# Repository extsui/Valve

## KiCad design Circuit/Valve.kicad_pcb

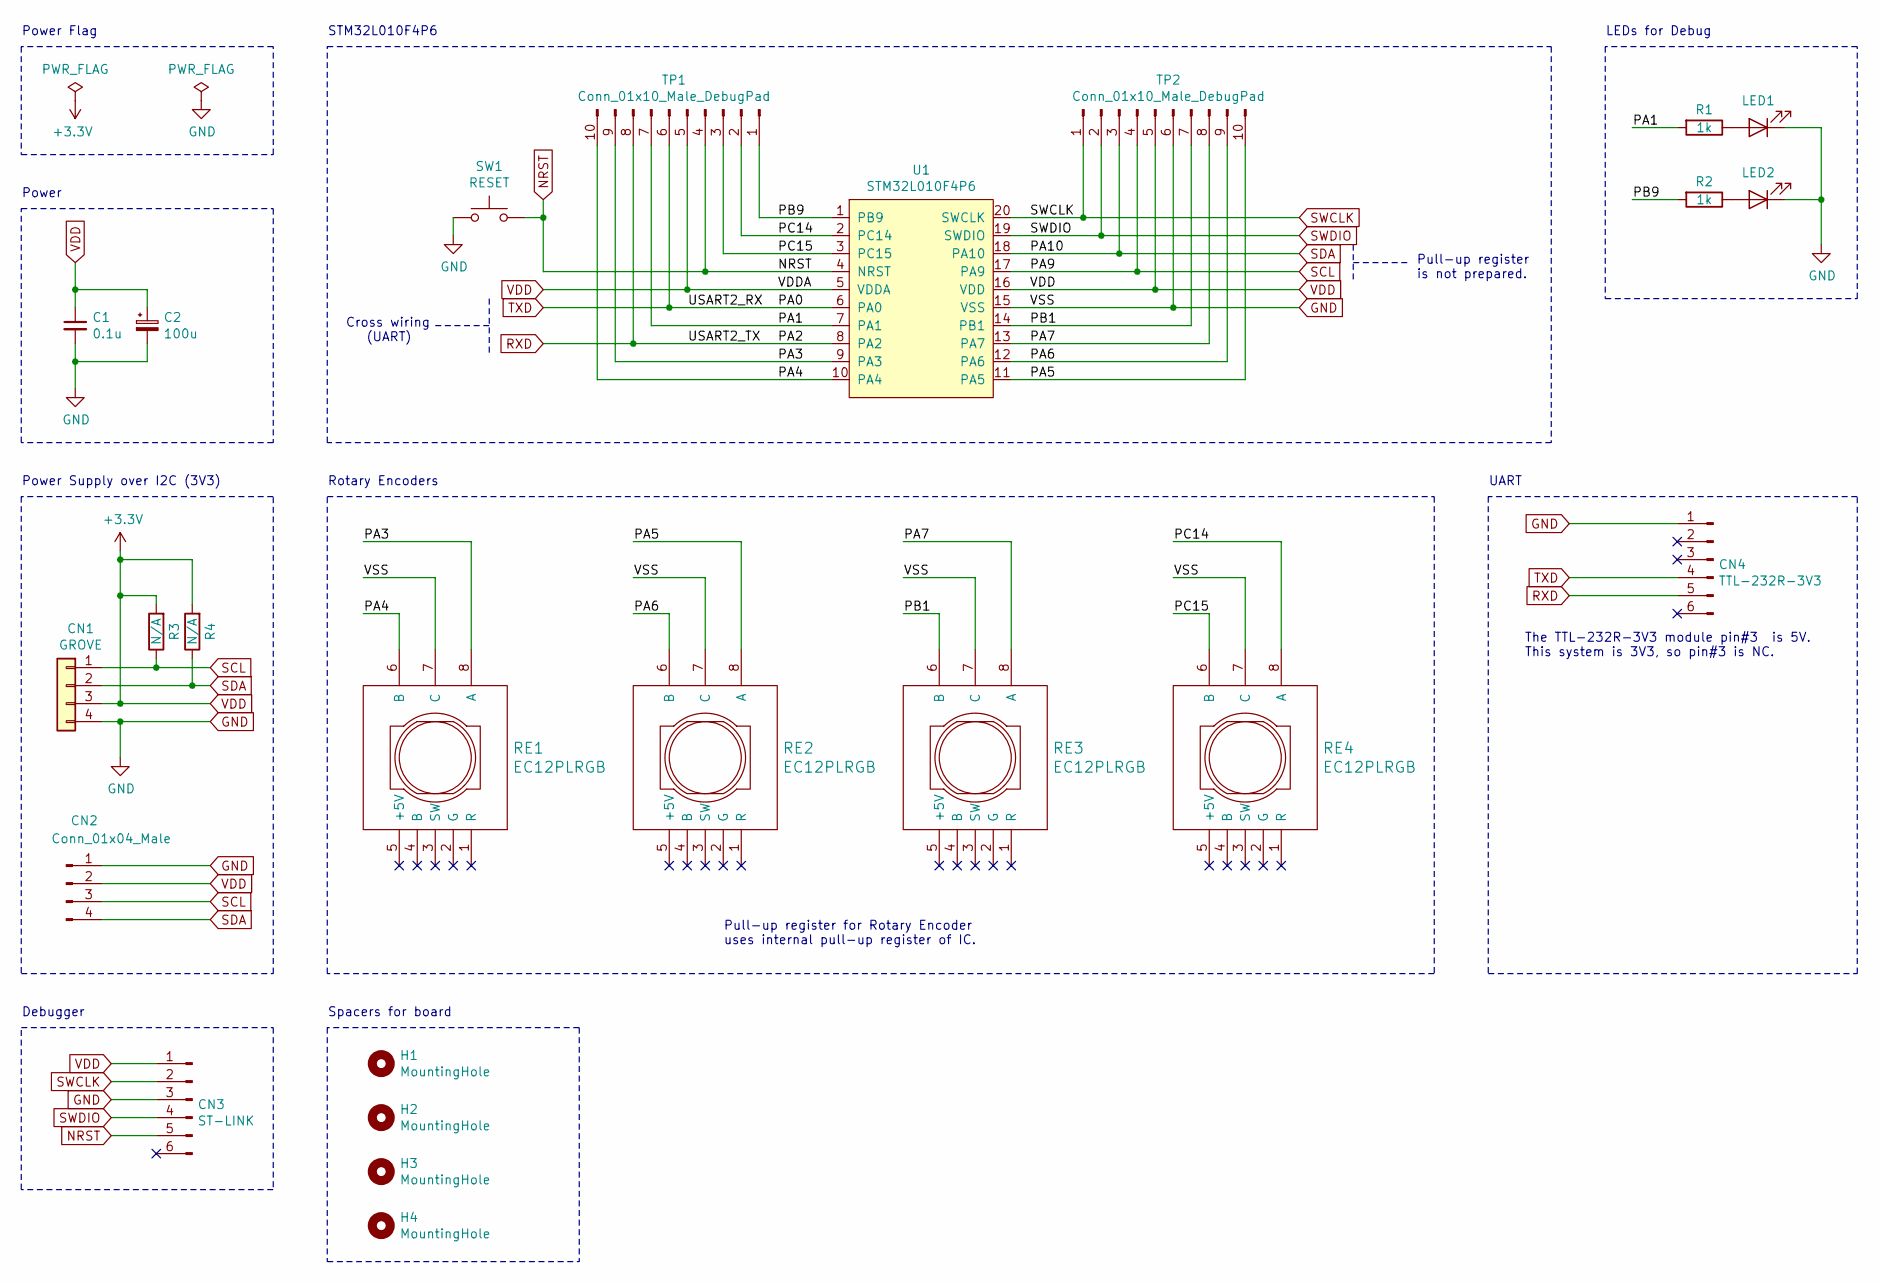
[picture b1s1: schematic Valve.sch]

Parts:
C1: 0.1u; C_Disc_D5.0mm_W2.5mm_P2.50mm
C2: 100u; CP_Radial_D6.3mm_P2.50mm
CN1: GROVE; HW4-2.0-90D
CN2: Conn_01x04_Male; PinHeader_1x04_P2.54mm_Vertical
CN3: ST-LINK; PinHeader_1x06_P2.54mm_Vertical
CN4: TTL-232R-3V3; PinHeader_1x06_P2.54mm_Vertical
H1, H2, H3, H4: MountingHole; MountingHole_3.2mm_M3
LED1, LED2: LED; LED_D3.0mm
R1, R2: 1k; R_Axial_DIN0207_L6.3mm_D2.5mm_P7.62mm_Horizontal
R3, R4: N/A; R_Axial_DIN0207_L6.3mm_D2.5mm_P7.62mm_Horizontal
RE1, RE2, RE3, RE4: EC12PLRGB
SW1: RESET; SW_PUSH_6mm_H8mm
TP1, TP2: Conn_01x10_Male_DebugPad; PinHeader_1x10_P2.54mm_Vertical
U1: STM32L010F4P6; TSSOP-20_4.4x6.5mm_P0.65mm

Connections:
/PA1: R1.2, TP1.7, U1.7 (PA1)
/PA3: RE1.8 (A), TP1.9, U1.9 (PA3)
/PA4: RE1.6 (B), TP1.10, U1.10 (PA4)
/PA5: RE2.8 (A), TP2.10, U1.11 (PA5)
/PA6: RE2.6 (B), TP2.9, U1.12 (PA6)
/PA7: RE3.8 (A), TP2.8, U1.13 (PA7)
/PB1: RE3.6 (B), TP2.7, U1.14 (PB1)
/PB9: R2.2, TP1.1, U1.1 (PB9)
/PC14: RE4.8 (A), TP1.2, U1.2 (PC14)
/PC15: RE4.6 (B), TP1.3, U1.3 (PC15)
GND: C1.2, C2.2, CN1.4, CN2.1, CN3.3, CN4.1, LED1.1 (K), LED2.1 (K), RE1.7 (C), RE2.7 (C), RE3.7 (C), RE4.7 (C), SW1.1, TP2.6, U1.15 (VSS)
NRST: CN3.5, SW1.2, TP1.4, U1.4 (NRST)
unnamed: LED1.2 (A), R1.1
unnamed: LED2.2 (A), R2.1
RXD: CN4.5, TP1.8, U1.8 (PA2)
SCL: CN1.1, CN2.3, R3.1, TP2.4, U1.17 (PA9)
SDA: CN1.2, CN2.4, R4.1, TP2.3, U1.18 (PA10)
SWCLK: CN3.2, TP2.1, U1.20 (SWCLK)
SWDIO: CN3.4, TP2.2, U1.19 (SWDIO)
TXD: CN4.4, TP1.6, U1.6 (PA0)
VDD: C1.1, C2.1, CN1.3, CN2.2, CN3.1, R3.2, R4.2, TP1.5, TP2.5, U1.5 (VDDA), U1.16 (VDD)

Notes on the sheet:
Cross wiring (UART)
The TTL-232R-3V3 module pin#3 is 5V. This system is 3V3, so pin#3 is NC.
Power Flag
Power Supply over I2C (3V3)
Spacers for board
Pull-up register is not prepared.
Pull-up register for Rotary Encoder uses internal pull-up register of IC.
Debugger
UART
Rotary Encoders
STM32L010F4P6
LEDs for Debug
Power

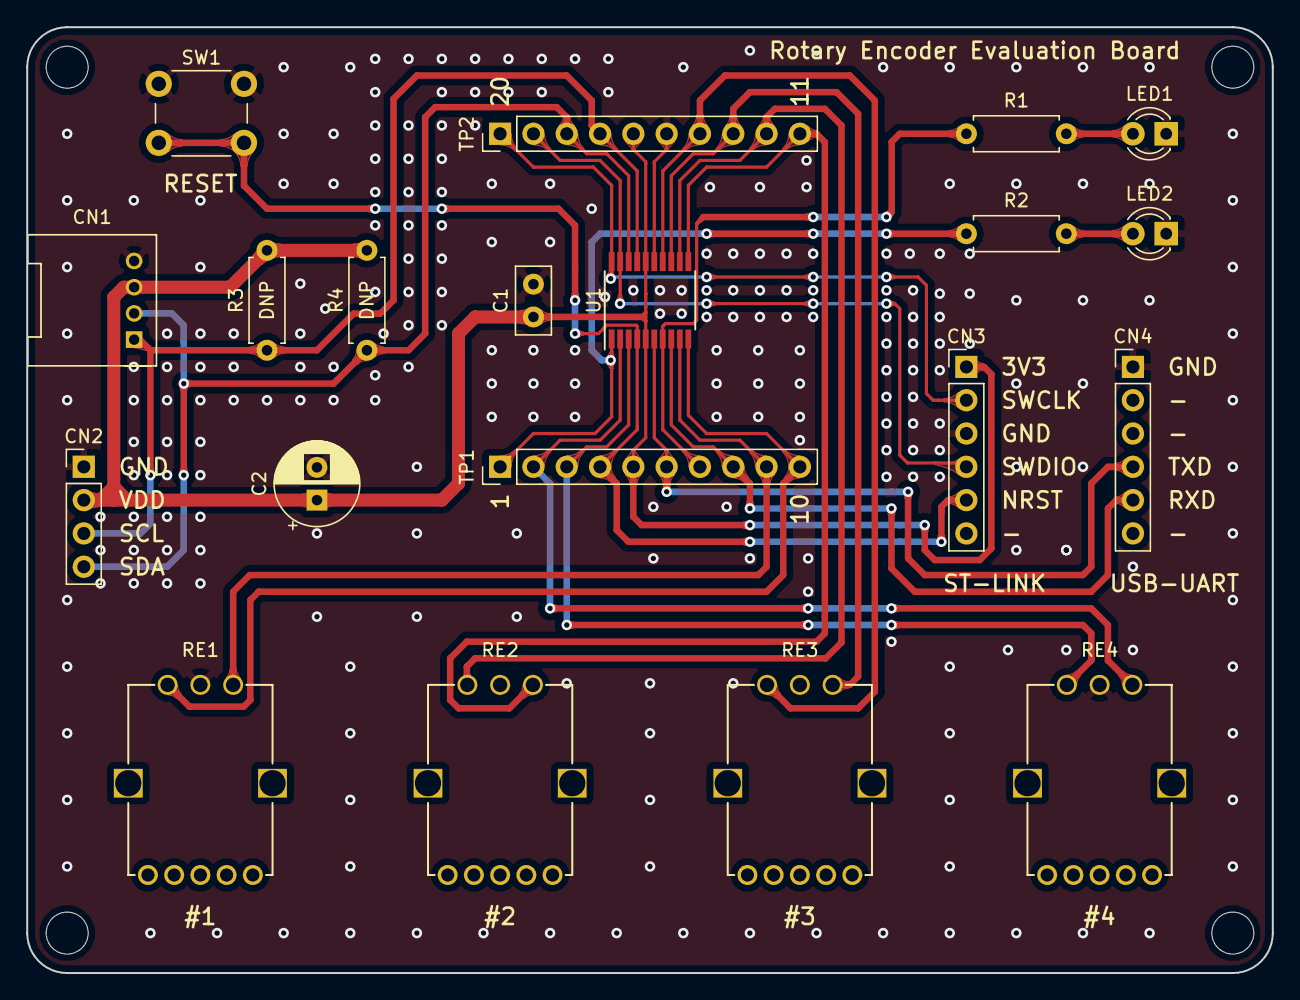
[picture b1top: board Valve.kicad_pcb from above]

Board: 2 copper layers, 95.0 x 72.1 mm, 24 parts (0 on the bottom side), 21 nets.

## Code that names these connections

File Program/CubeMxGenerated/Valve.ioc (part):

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Mcu.Name=STM32L010F4Px
Mcu.Package=TSSOP20
Mcu.UserName=STM32L010F4Px
PA0-CK_IN.Mode=Asynchronous
PA0-CK_IN.Signal=USART2_RX
PA1.GPIOParameters=GPIO_Label
PA1.GPIO_Label=LED1
PA1.Signal=GPIO_Output
PA10.Mode=I2C
PA10.Signal=I2C1_SDA
PA13.Mode=Serial_Wire
PA13.Signal=SYS_SWDIO
PA14.Mode=Serial_Wire
PA14.Signal=SYS_SWCLK
PA2.Mode=Asynchronous
PA2.Signal=USART2_TX
PA3.GPIOParameters=GPIO_PuPd,GPIO_Label
PA3.GPIO_Label=RotaryEncoder1A
PA3.GPIO_PuPd=GPIO_PULLUP
PA3.Signal=GPIO_Input
PA4.GPIOParameters=GPIO_PuPd,GPIO_Label
PA4.GPIO_Label=RotaryEncoder1B
PA4.GPIO_PuPd=GPIO_PULLUP
PA4.Signal=GPIO_Input
PA5.GPIOParameters=GPIO_PuPd,GPIO_Label
PA5.GPIO_Label=RotaryEncoder2A
PA5.GPIO_PuPd=GPIO_PULLUP
PA5.Signal=GPIO_Input
PA6.GPIOParameters=GPIO_PuPd,GPIO_Label
PA6.GPIO_Label=RotaryEncoder2B
PA6.GPIO_PuPd=GPIO_PULLUP
PA6.Signal=GPIO_Input
PA7.GPIOParameters=GPIO_PuPd,GPIO_Label
PA7.GPIO_Label=RotaryEncoder3A
PA7.GPIO_PuPd=GPIO_PULLUP
PA7.Signal=GPIO_Input
PA9.Mode=I2C
PA9.Signal=I2C1_SCL
PB1.GPIOParameters=GPIO_PuPd,GPIO_Label
PB1.GPIO_Label=RotaryEncoder3B
PB1.GPIO_PuPd=GPIO_PULLUP
PB1.Signal=GPIO_Input
PC14-OSC32_IN.GPIOParameters=GPIO_PuPd,GPIO_Label
PC14-OSC32_IN.GPIO_Label=RotaryEncoder4A
PC14-OSC32_IN.GPIO_PuPd=GPIO_PULLUP
PC14-OSC32_IN.Signal=GPIO_Input
PC15-OSC32_OUT.GPIOParameters=GPIO_PuPd,GPIO_Label
PC15-OSC32_OUT.GPIO_Label=RotaryEncoder4B
PC15-OSC32_OUT.GPIO_PuPd=GPIO_PULLUP
PC15-OSC32_OUT.Signal=GPIO_Input
RCC.HSE_VALUE=8000000
RCC.SYSCLKFreq_VALUE=32000000
RCC.SYSCLKSource=RCC_SYSCLKSOURCE_PLLCLK
board=custom

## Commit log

2021-12-20 KiCad のベースプロジェクトを登録
2021-12-24 回路図第一版の作成
2021-12-24 フットプリントの関連付け
2021-12-29 PCB 部品仮置き
2022-01-04 回路図を修正
    * 電源コネクタ (2P) を I2C 兼用 4P に変更
    * I2C ADDR パッドを削除して LED と抵抗に置換
2022-01-06 フットプリントにB基板外形を記載
2022-01-06 B基板外形状に部品仮置き
2022-01-07 フットプリントに説明シルクを追加
2022-01-07 I2C プルアップ抵抗 (DNP) を追加
2022-01-08 配線の全体仮組み
2022-01-11 配線を一通り接続完了
2022-01-11 U1 と TP1,2 間の配線を微細化
2022-01-12 斜め配線を削減して水平垂直配線に変換
2022-01-14 SWD に GND ガードを追加
2022-01-14 R1 用配線を SWD の上側を通すように修正
2022-01-14 I2C に GND ガードを追加
2022-01-15 GND ビア打ちとティアドロップ設定
2022-01-16 v1.0 のガーバーを作成
2022-01-17 Sample のテンプレを作成
2022-01-17 Valve ライブラリの試作 (動作未確認)
2022-01-18 Valve.Initialize() で疎通確認をするように修正
2022-03-05 MDK-ARM 生成物を追跡対象外に設定
2022-03-05 プログラムのベースプロジェクトを作成
2022-03-05 試作時のコードをポーティング
2022-03-05 vscode にインクルードパス設定ファイルを追加
2022-03-07 ロータリーエンコーダ動作で LED1 をトグルするように修正
2022-03-07 (ValveDemo) VisualStudioベースプロジェクトを作成
2022-03-08 (ValveDemo) OxyPlot をインストール
2022-03-13 (ValveDemo) スライダが連動するように修正
2022-03-13 (ValveDemo) Valve データ構造を追加
2022-03-13 (ValveDemo) COM ポート接続/切断を実装
2022-03-13 (ValveDemo) 送受信ログが自動スクロールされるように修正
2022-03-13 (ValveDemo) GUI レイアウト仮決め
2022-03-13 (ValveDemo) 送信ログを削除してデバッグログに転用
2022-03-14 (ValveDemo) エンコーダの値をスライダーの下に表示するように修正
2022-03-24 (ValveDemo) 受信ログが重たかったので ListBox に変更して軽量化
2022-03-25 (ValveDemo) Valve のキューを追加
2022-03-25 (ValveDemo) Encoder#1 のデータをグラフに連動
2022-03-25 (ValveDemo) 全ての Encoder をグラフに連動
2022-03-26 (Valve) 操作方向と逆に値が変化する不具合の解消 #1
    * 正確な原因は不明
    * 積算位置と差分反映のタイミングのズレが原因の可能性あり
    * Get()&Commit() の構造を単純化して Get() のみに変更して解決
2022-03-26 (ValveDemo) スライドバーの値域修正と操作不可能化
2022-03-26 (ValveDemo) タイムスタンプをグラフのX軸として使用するように修正
2022-03-26 (ValveDemo) グラフをリアルタイム描画に修正
    * X軸の時間範囲を追従
    * チェックボックスと各エンコーダの線グラフを連動
2022-03-26 (ValveDemo) グラフのサイズ調整と各エンコーダの色で連動を表現
2022-03-27 (ValveDemo) 受信ログ (ListBox) の自動スクロールを実装
2022-03-27 (ValveDemo) グラフ描画のリファクタリング
2022-03-27 (Valve) ロータリエンコーダに逆向き設定機能を追加 #2
2022-03-28 ロータリエンコーダの波形画像を追加
2022-04-13 (Valve) HAL_I2C を有効化
    * ビルドオプションが -O0 だと ROM に収まらなかったので -O2 に変更
2022-04-13 (Valve) I2C 受信データ解析と送信データ構築をメインコンテキストで行うように修正
2022-04-16 (Valve) I2C テスト用のデータ送信サンプルを作成
2022-04-17 (Valve) I2C 受信解析ハンドラを作成
2022-04-17 (Valve) I2C コマンドの全テストを追加
2022-04-17 (ValveDemo) C# で USB-CDC 経由のみシリアル受信ができない不具合を修正
2022-04-17 (Valve) 正転逆転を外部から指定可能に変更
2022-04-17 (ValveSample) XIAO USB-CDC 経由での ValveDemo 繋ぎこみ
2022-04-17 (Valve) デバッガの SWD クロックを 4MHz に修正
2022-04-19 (Valve) I2C スレーブドライバをメインから分離して整理
2022-04-19 ValveDemo のデモ動画を追加
2022-04-20 (Valve) ROM 削減のために TIM2 周期タイマを SysTick で置き換え
    * 約 1KiB の削減
2022-04-20 (Valve) I2C スレーブドライバに初期化アサートを追加
2022-04-20 (Valve) I2C スレーブドライバの受信コールバックを割り込みコンテキストに移動
